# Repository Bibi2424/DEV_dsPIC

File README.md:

DEV_dsPIC
=========

Author : DIB Guillaume

Beginning date : 05/2013

This is my SandBox :

There is all my work on DSPIC33F µC, Arduino and SolidWorks but this is a draft repo,
all important/elaborated sub-projects will have its own repo.

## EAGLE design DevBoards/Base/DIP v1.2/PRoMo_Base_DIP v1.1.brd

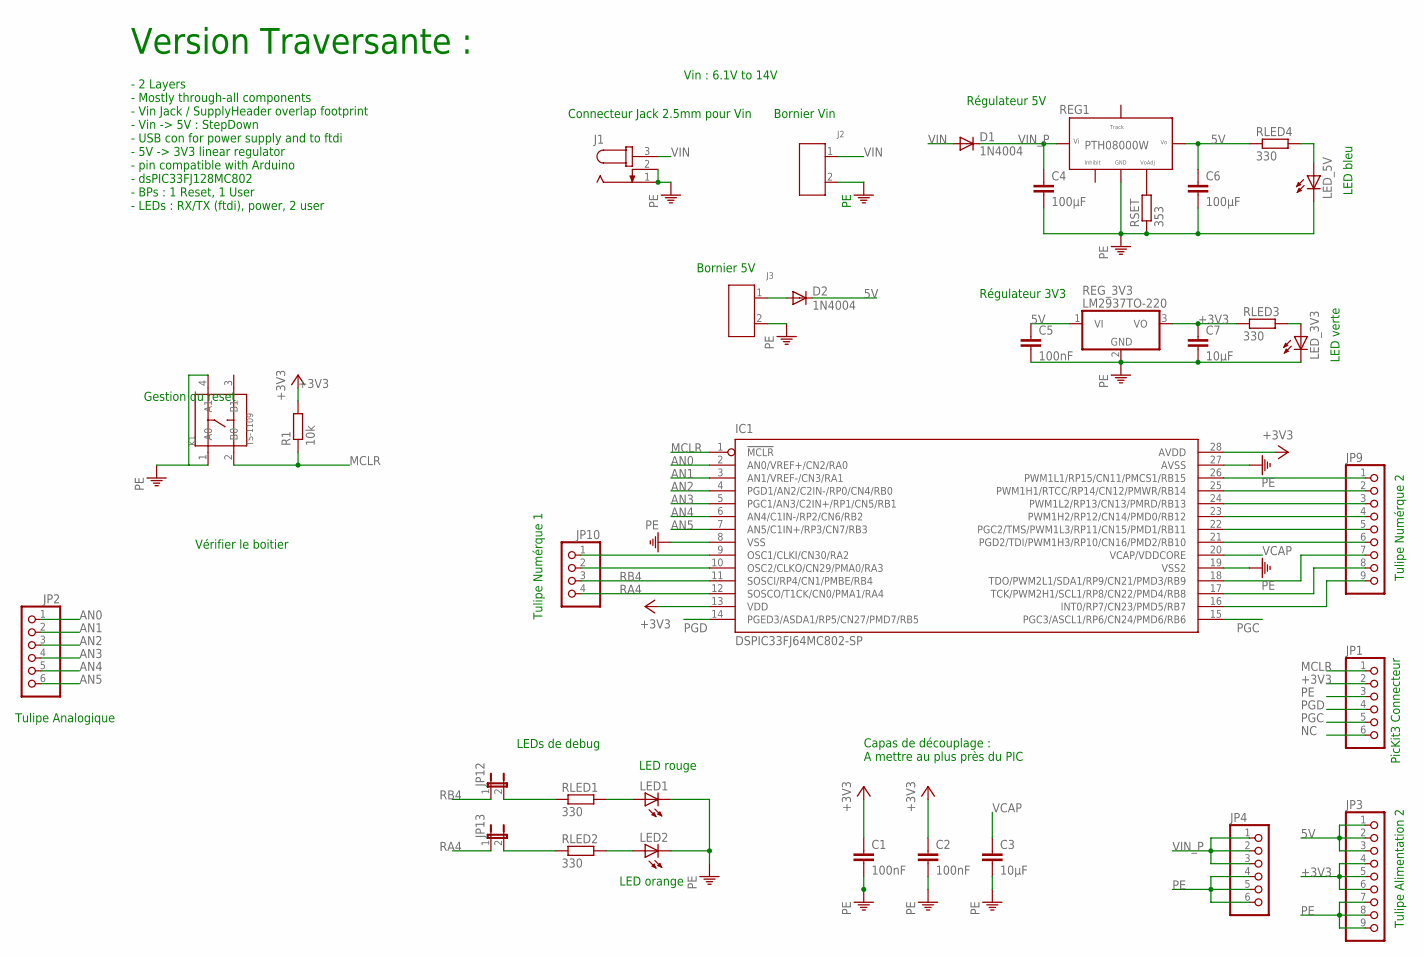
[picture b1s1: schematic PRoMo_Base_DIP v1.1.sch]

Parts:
C1: 100nF; C102-043X133
C2, C5: 100nF; C050-035X075
C3, C7: 10µF; C050-035X075
C4, C6: 100µF; C050-035X075
D1, D2: 1N4004; DO41-10
IC1: DSPIC33FJ64MC802-SP; DIL28-3
J1: JACK-PLUG1; SPC4078
J2, J3: SCREW-TERMINAL-GREEN(2P-5.0); H2-5.0-10.5X8.0MM
JP1: PINHD-1X6/90; 1X06/90
JP2, JP4: PINHD-1X6; 1X06
JP3, JP9: PINHD-1X9; 1X09
JP10: PINHD-1X4; 1X04
JP12, JP13: JP1E; JP1
K1: TS-1109; SW4-6.0X6.0X5.0MM
LED1, LED2: LED3MM
LED_3V3, LED_5V: LED3MM
R1: 10k; 0207/10
REG1: PTH08000W(EUS); TRHOUGH_HOLE_(EUS)
REG_3V3: LM2937TO-220; TO220V
RLED1, RLED2, RLED3, RLED4: 330; 0207/10
RSET: 353; 0207/10

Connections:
5V: C5.1, C6.1, D2.C, JP3.1, JP3.2, JP3.3, REG1.6, REG_3V3.1 (VI), RLED4.1
+3V3: C1.1, C2.1, C7.1, IC1.13 (VDD), IC1.28 (AVDD), JP1.2, JP3.4, JP3.5, JP3.6, R1.2, REG_3V3.3 (VO), RLED3.1
AN0: IC1.2 (AN0/VREF+/CN2/RA0), JP2.1
AN1: IC1.3 (AN1/VREF-/CN3/RA1), JP2.2
AN2: IC1.4 (PGD1/AN2/C2IN-/RP0/CN4/RB0), JP2.3
AN3: IC1.5 (PGC1/AN3/C2IN+/RP1/CN5/RB1), JP2.4
AN4: IC1.6 (AN4/C1IN-/RP2/CN6/RB2), JP2.5
AN5: IC1.7 (AN5/C1IN+/RP3/CN7/RB3), JP2.6
MCLR: IC1.1 (!MCLR), JP1.1, K1.2 (B0), R1.1
unnamed: IC1.26 (PWM1L1/RP15/CN11/PMCS1/RB15), JP9.1
unnamed: IC1.25 (PWM1H1/RTCC/RP14/CN12/PMWR/RB14), JP9.2
unnamed: IC1.24 (PWM1L2/RP13/CN13/PMRD/RB13), JP9.3
unnamed: IC1.23 (PWM1H2/RP12/CN14/PMD0/RB12), JP9.4
unnamed: IC1.22 (PGC2/TMS/PWM1L3/RP11/CN15/PMD1/RB11), JP9.5
unnamed: IC1.21 (PGD2/TDI/PWM1H3/RP10/CN16/PMD2/RB10), JP9.6
unnamed: IC1.18 (TDO/PWM2L1/SDA1/RP9/CN21/PMD3/RB9), JP9.7
unnamed: IC1.17 (TCK/PWM2H1/SCL1/RP8/CN22/PMD4/RB8), JP9.8
unnamed: IC1.16 (INT0/RP7/CN23/PMD5/RB7), JP9.9
unnamed: IC1.9 (OSC1/CLKI/CN30/RA2), JP10.1
unnamed: IC1.10 (OSC2/CLKO/CN29/PMA0/RA3), JP10.2
unnamed: LED2.A, RLED2.2
unnamed: LED1.A, RLED1.2
unnamed: LED_3V3.A, RLED3.2
unnamed: JP12.2, RLED1.1
unnamed: JP13.2, RLED2.1
unnamed: D2.A, J3.1
unnamed: REG1.5, RSET.2
unnamed: LED_5V.A, RLED4.2
NC: JP1.6
PE: C1.2, C2.2, C3.2, C4.2, C5.2, C6.2, C7.2, IC1.8 (VSS), IC1.19 (VSS2), IC1.27 (AVSS), J1.1, J1.2, J2.2, J3.2, JP1.3, JP3.7, JP3.8, JP3.9, JP4.4, JP4.5, JP4.6, K1.1 (A0), K1.4 (A1), LED1.K (C), LED2.K (C), LED_3V3.K (C), LED_5V.K (C), REG1.1, REG_3V3.2 (GND), RSET.1
PGC: IC1.15 (PGC3/ASCL1/RP6/CN24/PMD6/RB6), JP1.5
PGD: IC1.14 (PGED3/ASDA1/RP5/CN27/PMD7/RB5), JP1.4
RA4: IC1.12 (SOSCO/T1CK/CN0/PMA1/RA4), JP10.4, JP13.1
RB4: IC1.11 (SOSCI/RP4/CN1/PMBE/RB4), JP10.3, JP12.1
VCAP: C3.1, IC1.20 (VCAP/VDDCORE)
VIN: D1.A, J1.3, J2.1
VIN_P: C4.1, D1.C, JP4.1, JP4.2, JP4.3, REG1.3

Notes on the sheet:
PicKit3 Connecteur
Capas de découplage : A mettre au plus près du PIC
Gestion du reset
Version Traversante :
Vérifier le boitier
- 2 Layers - Mostly through-all components - Vin Jack / SupplyHeader overlap footprint - Vin -> 5V : StepDown - USB con for power supply and to ftdi - 5V -> 3V3 linear regulator - pin compatible with Arduino - dsPIC33FJ128MC802 - BPs : 1 Reset, 1 User - LEDs : RX/TX (ftdi), power, 2 user
Connecteur Jack 2.5mm pour Vin
Régulateur 5V
Régulateur 3V3
Tulipe Analogique
Tulipe Numérque 1
Tulipe Numérque 2
Tulipe Alimentation 2
LEDs de debug
Vin : 6.1V to 14V
Bornier Vin
Bornier 5V
LED bleu
LED verte
LED rouge
LED orange

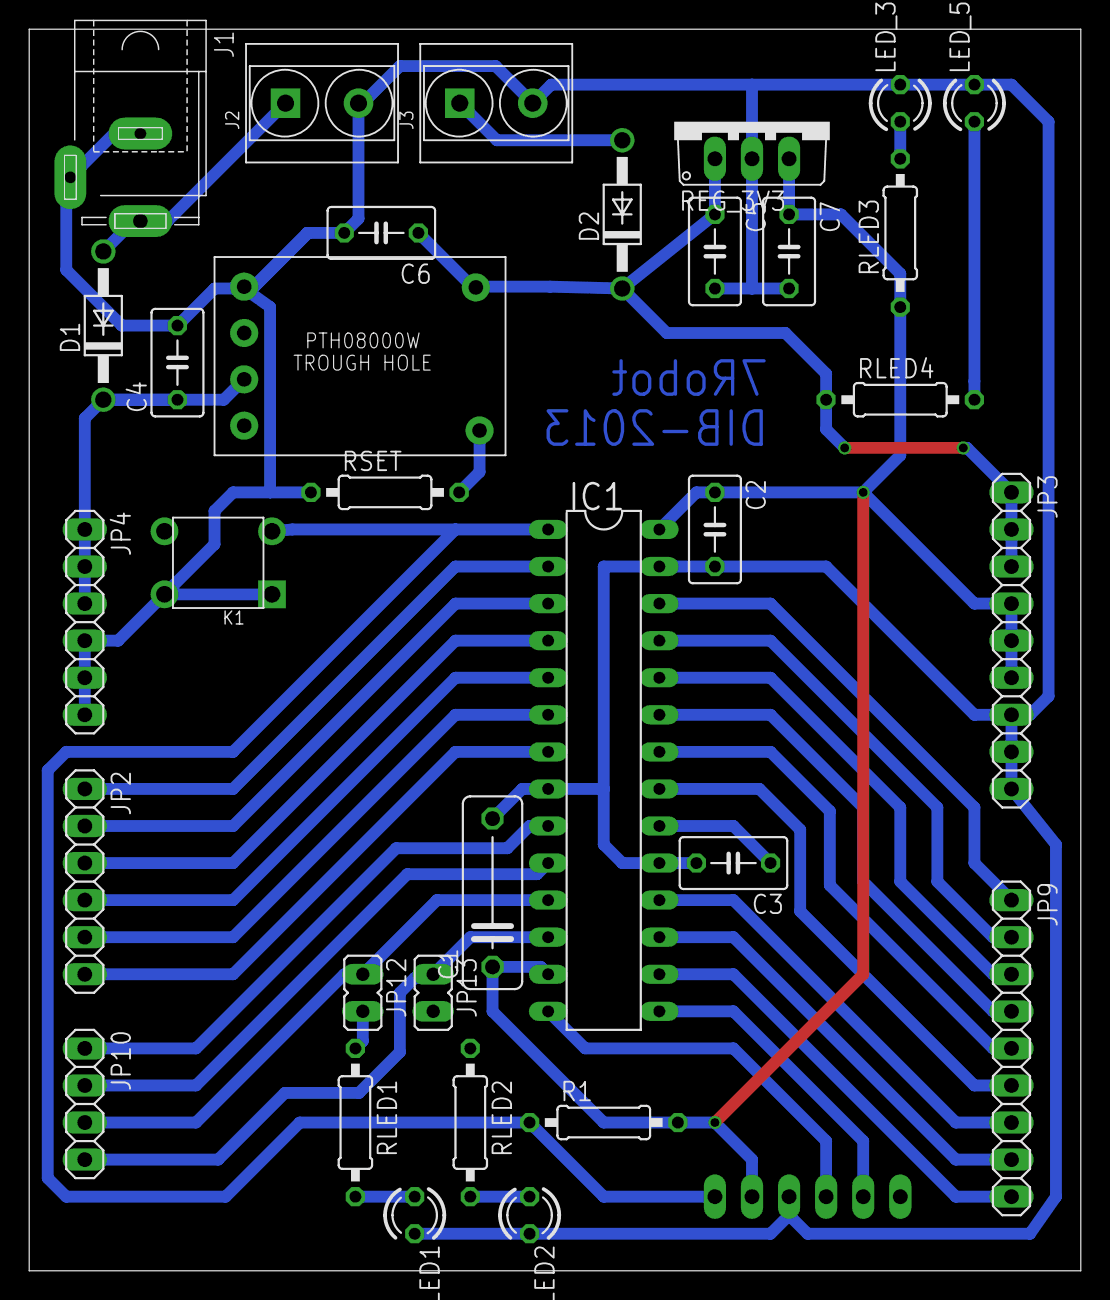
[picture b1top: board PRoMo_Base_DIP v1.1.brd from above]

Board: 2 copper layers, 72.1 x 85.1 mm, 34 parts (1 on the bottom side), 36 nets.

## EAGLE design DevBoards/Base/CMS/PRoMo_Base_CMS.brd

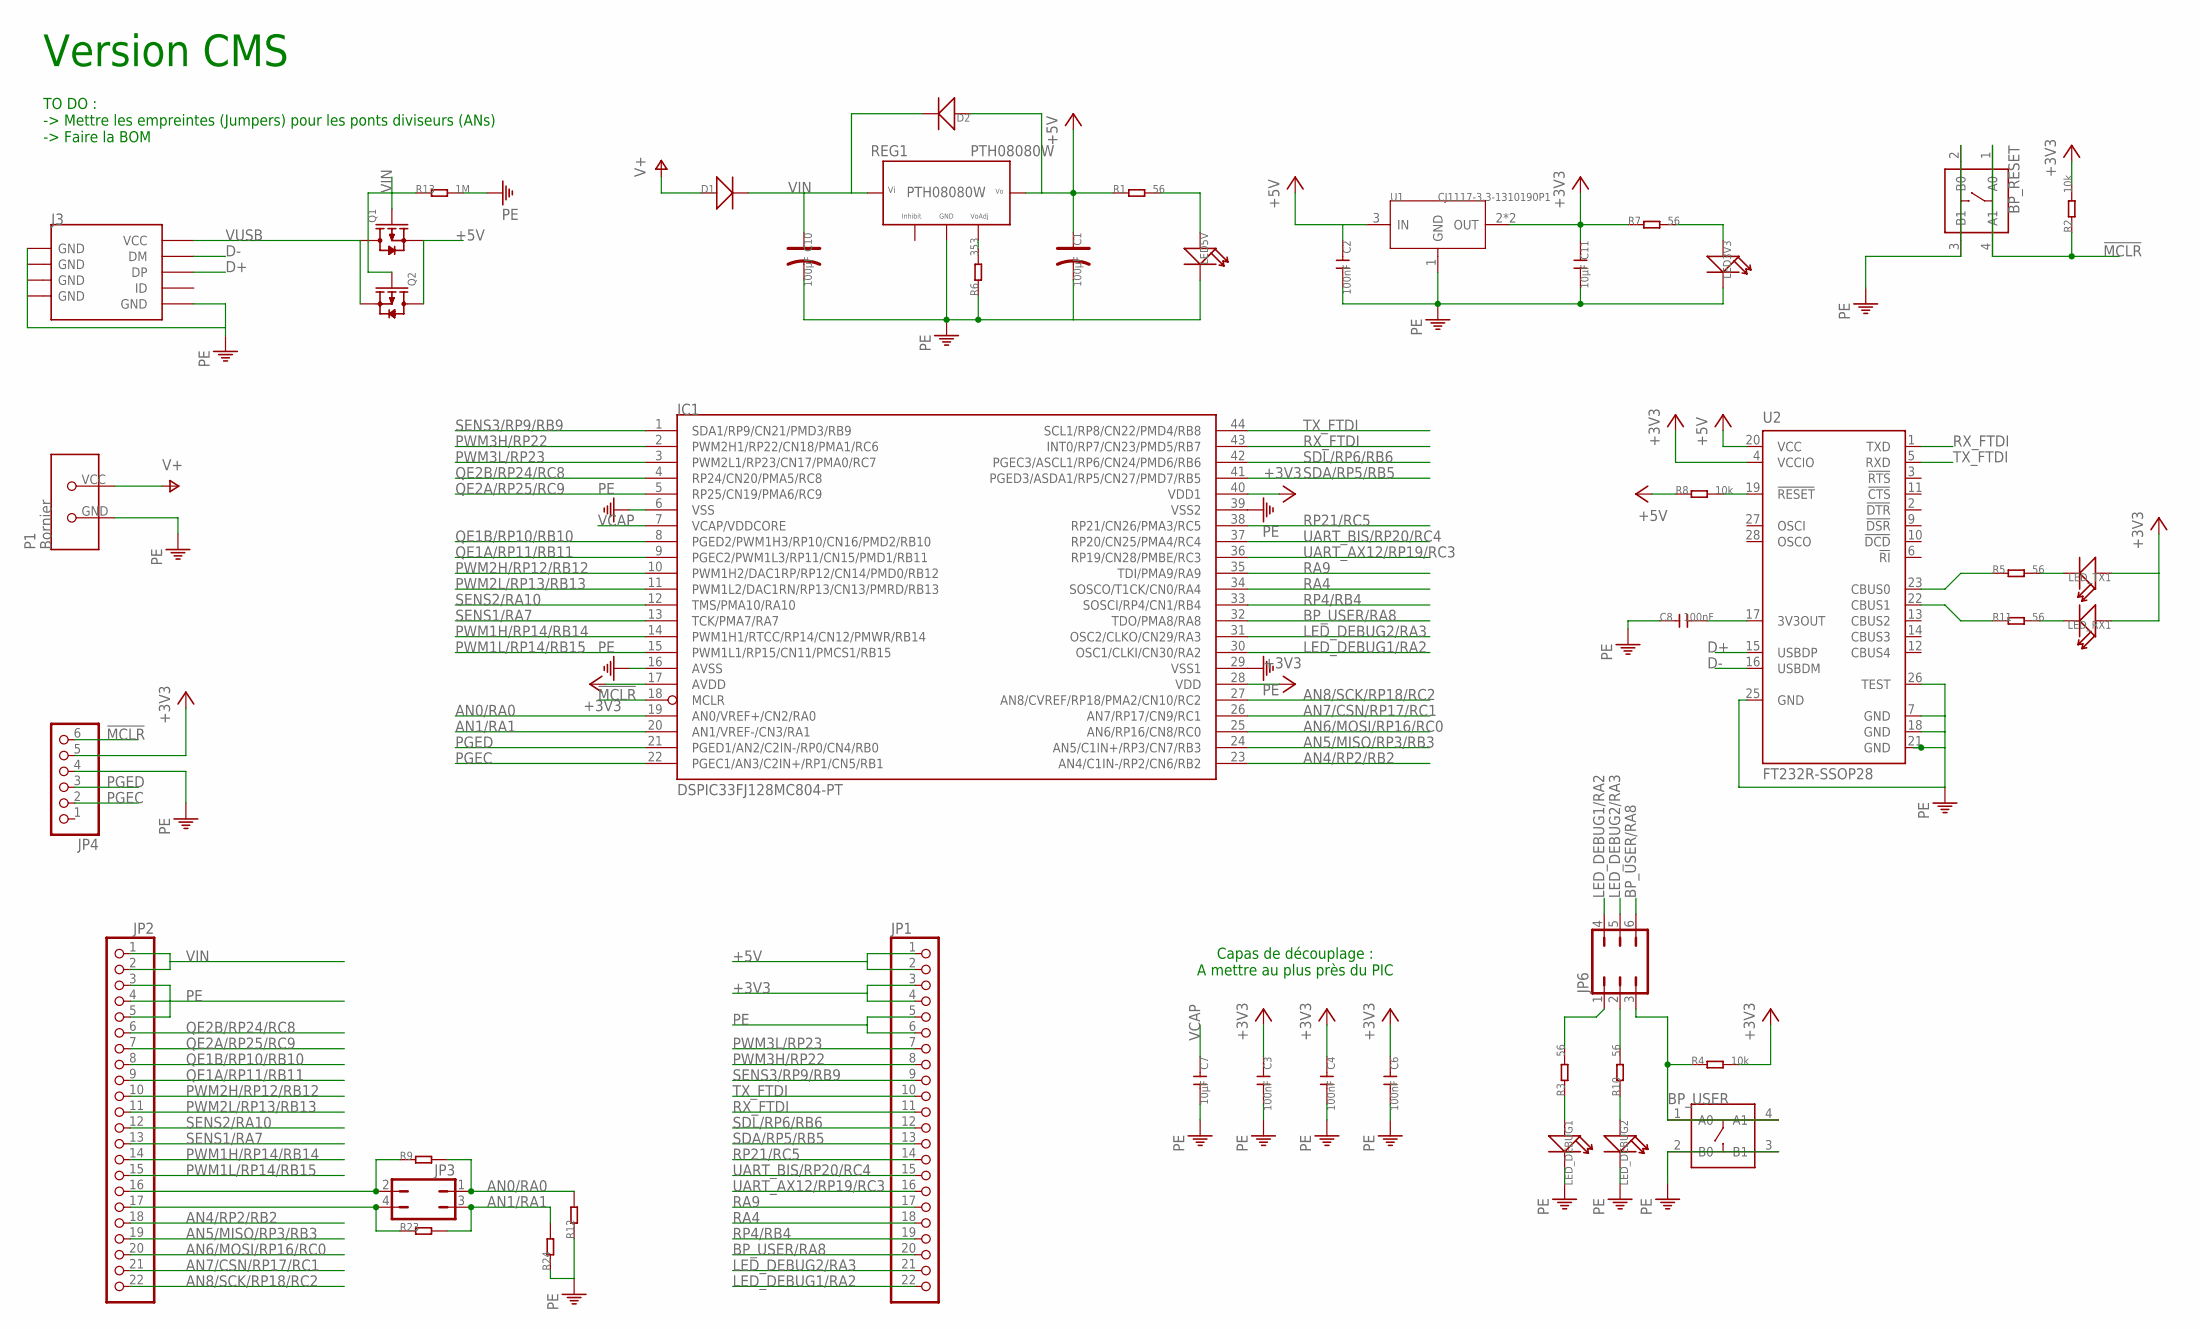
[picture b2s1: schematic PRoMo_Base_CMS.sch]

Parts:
BP_RESET: BUTTON-4P-6.2X6.2; 4P-6.2X6.2
BP_USER: BUTTON-4P-6.2X6.2; 4P-6.2X6.2
C1, C10: 100µF; ELECTRO-5.3MM
C2, C3, C4, C6, C8: 100nF; C0805
C7, C11: 10µF; C0805
D1, D2: D'1206'; SOD123
IC1: DSPIC33FJ128MC804-PT; TQFP44
J3: USB-MINIUSB-5P-TH; MINI-5P
JP1, JP2: PINHD-1X22; 1X22
JP3: JP2Q
JP4: PINHD-1X6/90; 1X06/90
JP6: JP3Q
LED3V3, LED5V: LED'1206'; LED-1206
LED_DEBUG1, LED_DEBUG2: LED'1206'; LED-1206
LED_RX1: LED'1206'; LED-1206
LED_TX1: LED'1206'; LED-1206
P1: Bornier; BORNIER_COUDEE_3.5
Q1, Q2: MOSFET-P'SI2323CDS/SI2305DS<BR>'; SOT23
R1, R3, R5, R7, R10, R11: 56; R0805
R2, R4, R8: 10k; R0805
R6: 353; R0204/7
R9, R12, R23, R24: R-0805; R0805
R13: 1M; R0805
REG1: PTH08080W
U1: CJ1117-3.3-1310190P1; SOT223
U2: FT232R-SSOP28; SSOP28

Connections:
!MCLR!: BP_RESET.1 (A0), BP_RESET.4 (A1), IC1.18 (MCLR), JP4.6, R2.1
+3V3: C3.1, C4.1, C6.1, C11.1, IC1.17 (AVDD), IC1.28 (VDD), IC1.40 (VDD1), JP1.3, JP1.4, JP4.5, LED_RX1.+, LED_TX1.+, R2.2, R4.2, R7.1, U1.2 (OUT), U1.TER (OUT), U2.4 (VCCIO)
+5V: C1.+, C2.1, D2.+, JP1.1, JP1.2, Q1.2 (S), Q2.3 (D), R1.1, R8.1, REG1.P$3 (3_VO), U1.3 (IN), U2.20 (VCC)
AN0/RA0: IC1.19 (AN0/VREF+/CN2/RA0), JP3.1, R9.2, R12.2
AN1/RA1: IC1.20 (AN1/VREF-/CN3/RA1), JP3.3, R23.2, R24.2
AN4/RP2/RB2: IC1.23 (AN4/C1IN-/RP2/CN6/RB2), JP2.18
AN5/MISO/RP3/RB3: IC1.24 (AN5/C1IN+/RP3/CN7/RB3), JP2.19
AN6/MOSI/RP16/RC0: IC1.25 (AN6/RP16/CN8/RC0), JP2.20
AN7/CSN/RP17/RC1: IC1.26 (AN7/RP17/CN9/RC1), JP2.21
AN8/SCK/RP18/RC2: IC1.27 (AN8/CVREF/RP18/PMA2/CN10/RC2), JP2.22
BP: BP_USER.1 (A0), BP_USER.4 (A1), JP6.3, R4.1
BP_USER/RA8: IC1.32 (TDO/PMA8/RA8), JP1.20, JP6.6
D+: J3.DP, U2.15 (USBDP)
D-: J3.DM, U2.16 (USBDM)
LED_DEBUG1/RA2: IC1.30 (OSC1/CLKI/CN30/RA2), JP1.22, JP6.4
LED_DEBUG2/RA3: IC1.31 (OSC2/CLKO/CN29/RA3), JP1.21, JP6.5
unnamed: R6.2, REG1.P$4 (4_VOADJ)
unnamed: LED5V.+, R1.2
unnamed: LED_DEBUG1.+, R3.1
unnamed: JP6.1, R3.2
unnamed: LED3V3.+, R7.2
unnamed: C8.2, U2.17 (3V3OUT)
unnamed: R8.2, U2.19 (!RESET)
unnamed: JP2.17, JP3.4, R23.1
unnamed: JP2.16, JP3.2, R9.1
unnamed: R11.1, U2.22 (CBUS1)
unnamed: R5.1, U2.23 (CBUS0)
unnamed: LED_DEBUG2.+, R10.1
unnamed: LED_TX1.-, R5.2
unnamed: JP6.2, R10.2
unnamed: LED_RX1.-, R11.2
PE: BP_RESET.2 (B0), BP_RESET.3 (B1), BP_USER.2 (B0), BP_USER.3 (B1), C1.-, C2.2, C3.2, C4.2, C6.2, C7.2, C8.1, C10.-, C11.2, IC1.6 (VSS), IC1.16 (AVSS), IC1.29 (VSS1), IC1.39 (VSS2), J3.GND, J3.S1 (GND), J3.S2 (GND), J3.S3 (GND), J3.S4 (GND), JP1.5, JP1.6, JP2.3, JP2.4, JP2.5, JP4.4, LED3V3.-, LED5V.-, LED_DEBUG1.-, LED_DEBUG2.-, P1.GND, R6.1, R12.1, R13.2, R24.1, REG1.P$2 (2_GND), U1.1 (GND), U2.7 (GND), U2.18 (GND), U2.21 (GND), U2.25 (GND), U2.26 (TEST)
PGEC: IC1.22 (PGEC1/AN3/C2IN+/RP1/CN5/RB1), JP4.2
PGED: IC1.21 (PGED1/AN2/C2IN-/RP0/CN4/RB0), JP4.3
PWM1H/RP14/RB14: IC1.14 (PWM1H1/RTCC/RP14/CN12/PMWR/RB14), JP2.14
PWM1L/RP14/RB15: IC1.15 (PWM1L1/RP15/CN11/PMCS1/RB15), JP2.15
PWM2H/RP12/RB12: IC1.10 (PWM1H2/DAC1RP/RP12/CN14/PMD0/RB12), JP2.10
PWM2L/RP13/RB13: IC1.11 (PWM1L2/DAC1RN/RP13/CN13/PMRD/RB13), JP2.11
PWM3H/RP22: IC1.2 (PWM2H1/RP22/CN18/PMA1/RC6), JP1.8
PWM3L/RP23: IC1.3 (PWM2L1/RP23/CN17/PMA0/RC7), JP1.7
QE1A/RP11/RB11: IC1.9 (PGEC2/PWM1L3/RP11/CN15/PMD1/RB11), JP2.9
QE1B/RP10/RB10: IC1.8 (PGED2/PWM1H3/RP10/CN16/PMD2/RB10), JP2.8
QE2A/RP25/RC9: IC1.5 (RP25/CN19/PMA6/RC9), JP2.7
QE2B/RP24/RC8: IC1.4 (RP24/CN20/PMA5/RC8), JP2.6
RA4: IC1.34 (SOSCO/T1CK/CN0/RA4), JP1.18
RA9: IC1.35 (TDI/PMA9/RA9), JP1.17
RP4/RB4: IC1.33 (SOSCI/RP4/CN1/RB4), JP1.19
RP21/RC5: IC1.38 (RP21/CN26/PMA3/RC5), JP1.14
RX_FTDI: IC1.43 (INT0/RP7/CN23/PMD5/RB7), JP1.11, U2.1 (TXD)
SDA/RP5/RB5: IC1.41 (PGED3/ASDA1/RP5/CN27/PMD7/RB5), JP1.13
SDL/RP6/RB6: IC1.42 (PGEC3/ASCL1/RP6/CN24/PMD6/RB6), JP1.12
SENS1/RA7: IC1.13 (TCK/PMA7/RA7), JP2.13
SENS2/RA10: IC1.12 (TMS/PMA10/RA10), JP2.12
SENS3/RP9/RB9: IC1.1 (SDA1/RP9/CN21/PMD3/RB9), JP1.9
TX_FTDI: IC1.44 (SCL1/RP8/CN22/PMD4/RB8), JP1.10, U2.5 (RXD)
UART_AX12/RP19/RC3: IC1.36 (RP19/CN28/PMBE/RC3), JP1.16
UART_BIS/RP20/RC4: IC1.37 (RP20/CN25/PMA4/RC4), JP1.15
V+: D1.+, P1.VCC
VCAP: C7.1, IC1.7 (VCAP/VDDCORE)
VIN: C10.+, D1.-, D2.-, JP2.1, JP2.2, Q1.1 (G), Q2.1 (G), R13.1, REG1.P$1 (1_VI)
VUSB: J3.VCC, Q1.3 (D), Q2.2 (S)

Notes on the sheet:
Version CMS
TO DO : -> Mettre les empreintes (Jumpers) pour les ponts diviseurs (ANs) -> Faire la BOM
Capas de découplage : A mettre au plus près du PIC

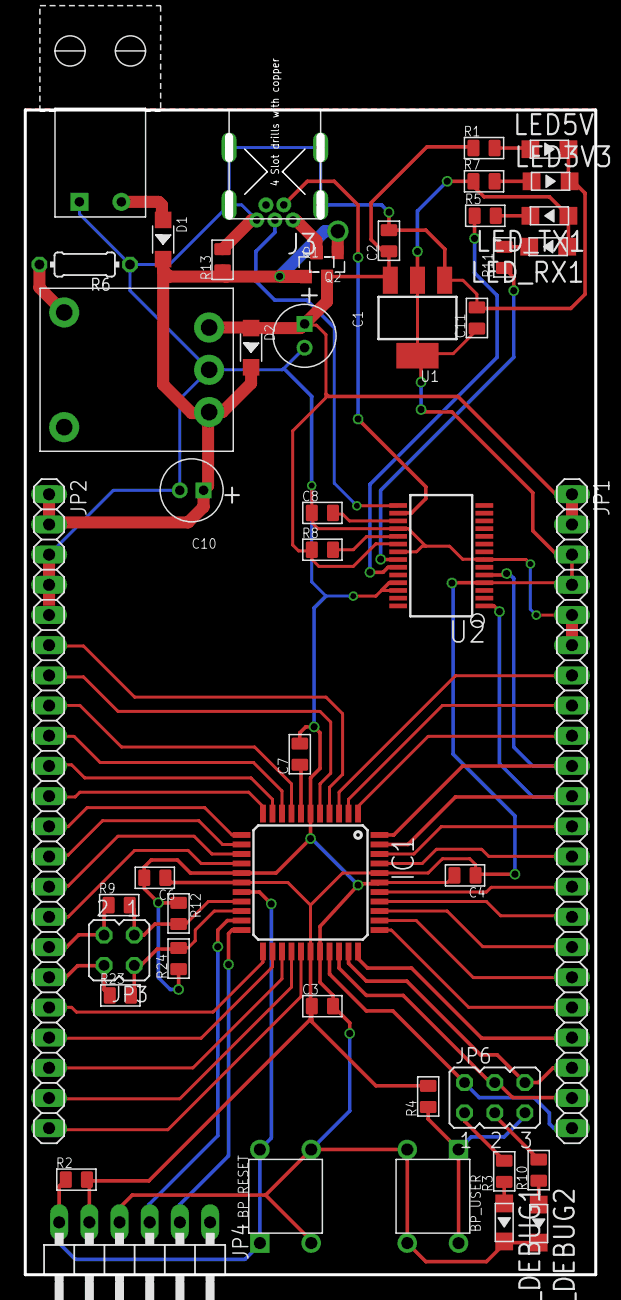
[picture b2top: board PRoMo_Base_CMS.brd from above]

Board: 2 copper layers, 48.0 x 98.0 mm, 47 parts (0 on the bottom side), 61 nets.

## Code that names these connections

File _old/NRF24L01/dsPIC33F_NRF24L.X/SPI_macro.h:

/*
* dsPIC33F & module NRF24L
* Compiler : Microchip xC16
* µC : 33FJ64MC802
* File : SPI_macro.h
* Juin 2013
*    ____________      _           _
*   |___  /| ___ \    | |         | |
*      / / | |_/ /___ | |__   ___ | |_
*     / /  |    // _ \| '_ \ / _ \| __|
*    / /   | |\ \ (_) | |_) | (_) | |_
*   /_/    |_| \_\___/|____/ \___/'\__|
*			      7robot.fr
*/

#ifndef SPI_MACRO_H
#define	SPI_MACRO_H

//Defines
#define SPI_SCK _RB5        // Clock outpout pin,
#define SPI_SO _RB6         // Serial output pin,
#define SPI_SI _RB7         // Serial input pin,
#define SPI_CSN _RB8        // CSN output pin,
#define SPI_CE _RB9         // CE output pin,
#define SPI_IRQ _LATB10       // IRQ input pin,

//Prototypes
void InitSPI(void);

#endif	/* SPI_H */

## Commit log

2013-05-19 Base dsPIC v1.1 & Shield Moteur sans connecteur
2013-05-19 Updated README and gitignore
2013-05-19 Je vais m'en sortir avec ce REAME
2013-05-19 Encore un petit changement sur ce README
2013-05-19 Last change on the README file
2013-05-19 Ou pas
2013-05-20 Ajout des trous pour fixation de la carte
2013-05-20 Ajout du tuto
2013-05-21 Petit changement au routage et au template
2013-05-21 Carte de DEV base presque finit
2013-08-27 Ajout du projet de base roulante SolidWorks
2013-09-27 Fusion avec l'ancien repo 7robot
2013-09-28 Ajout de la lib de controle de servo
2013-09-29 Ajout du template v2
    pas encore terminer, il manque le parseur UART
2013-10-02 Ajout du projet ruban led
2014-02-18 Test StripLed et Ajout SLD Robinch
2014-02-27 Sld 7Robinch V2
2014-03-29 Sld 7Robinch V3
2014-04-24 Ajout Debug Matlab
2014-04-24 Ajout Joystick
2014-05-09 Ajout MakerFaire et MAJ dsPIC 7robinch
2014-05-20 Canon OK
2014-05-24 Avancement Sick
2014-06-18 Update CdF
2014-09-20 Update LedStrip Arduino code
2016-11-15 Massive clean up
